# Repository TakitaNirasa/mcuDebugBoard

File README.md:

# Отладочная плата
### Назначение
Унивесальная плата для разработки простых дешёвых встраиваемых устройств либо как вспомагательная плата в более сложной системе.
Архитектура платы представлена ниже:

### Задачи поставленные перед платой:
  * Максимальная дешивизна и простота в покупке компонентов
  * "Универсальность без излишеств"
  * Возможность подключения периферии без мотка проводов
  * Наличие как обычного ввода-вывода, так и опторазвязанного
  * Наличие "силовой части" управления нагрузкой
  * Кнопки и индикация на плате
  * Модуль зарядки аккумулятора с защитой

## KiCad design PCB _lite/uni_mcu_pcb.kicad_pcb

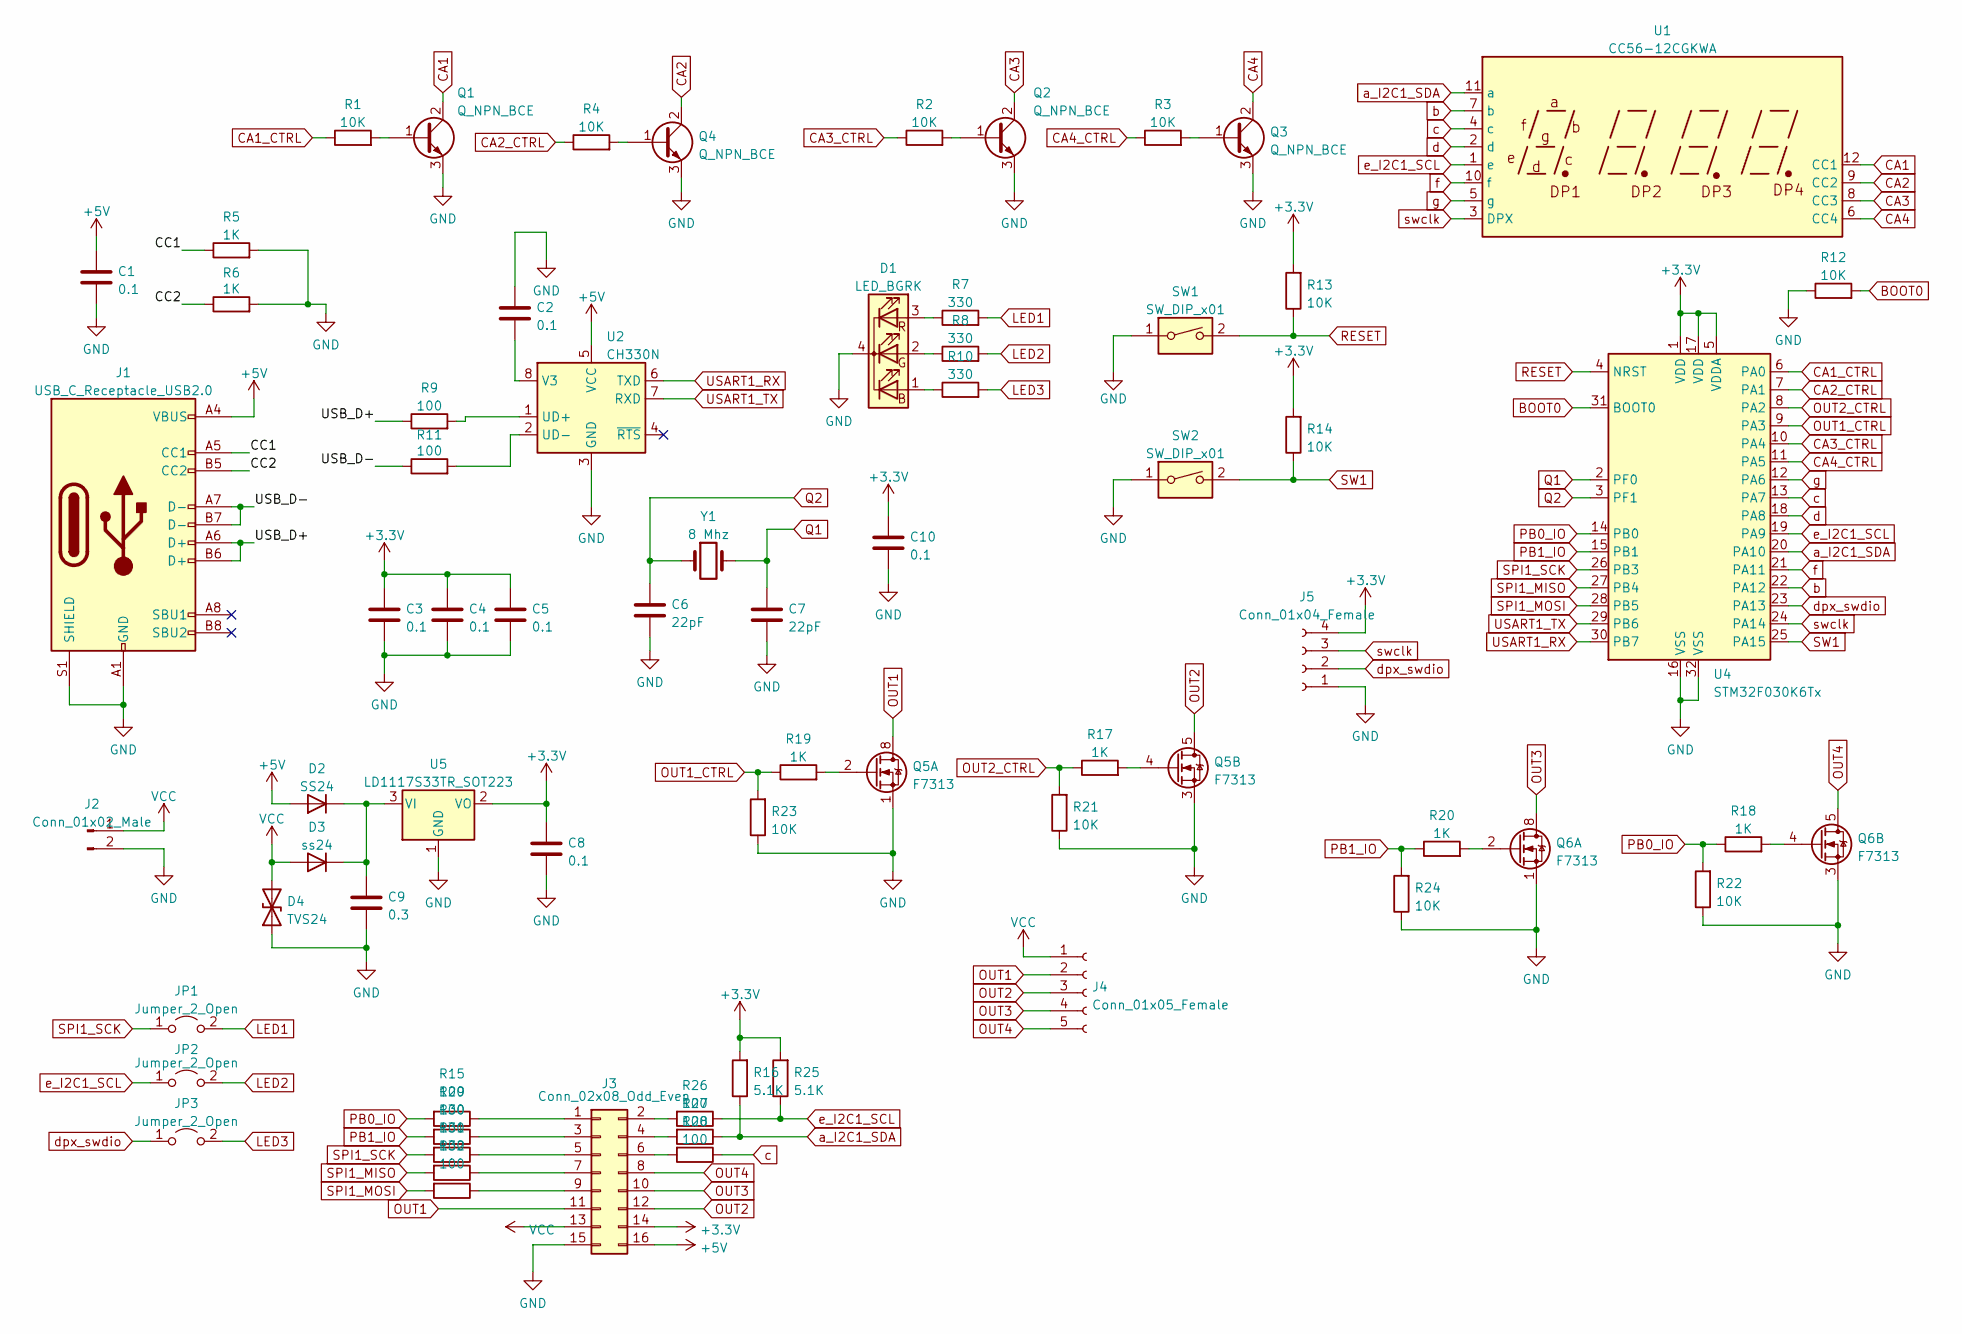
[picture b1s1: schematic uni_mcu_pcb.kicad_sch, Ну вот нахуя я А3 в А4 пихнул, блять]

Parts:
C1, C2, C3, C4, C5, C8, C10: 0.1; C_0603_1608Metric_Pad1.08x0.95mm_HandSolder
C6, C7: 22pF; C_0603_1608Metric_Pad1.08x0.95mm_HandSolder
C9: 0.3; C_0603_1608Metric_Pad1.08x0.95mm_HandSolder
D1: LED_BGRK; LED_RGB_1210
D2: SS24; D_SMB
D3: ss24; D_SMB
D4: TVS24; D_SMB
J1: USB_C_Receptacle_USB2.0; USB_C_Receptacle_GCT_USB4105-xx-A_16P_TopMnt_Horizontal
J2: Conn_01x02_Male; TerminalBlock_MetzConnect_Type011_RT05502HBWC_1x02_P5.00mm_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
J3: Conn_02x08_Odd_Even; IDC-Header_2x08_P2.54mm_Vertical
J4: Conn_01x05_Female; TerminalBlock_MetzConnect_Type011_RT05505HBWC_1x05_P5.00mm_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
J5: Conn_01x04_Female; Hirose_DF11-4DP-2DSA_2x02_P2.00mm_Vertical
JP1, JP2, JP3: Jumper_2_Open; SolderJumper-2_P1.3mm_Open_TrianglePad1.0x1.5mm
Q1, Q2, Q3, Q4: Q_NPN_BCE; SOT-23-3
Q5, Q6: F7313; SOIC-8_3.9x4.9mm_P1.27mm
R1, R2, R3, R4, R12, R13, R14, R21, R22, R23, R24: 10K; R_0603_1608Metric_Pad0.98x0.95mm_HandSolder
R5, R6, R17, R18, R19, R20: 1K; R_0603_1608Metric_Pad0.98x0.95mm_HandSolder
R7, R8, R10: 330; R_0603_1608Metric_Pad0.98x0.95mm_HandSolder
R9, R11, R15, R26, R27, R28, R29, R30, R31, R32: 100; R_0603_1608Metric_Pad0.98x0.95mm_HandSolder
R16, R25: 5.1K; R_0603_1608Metric_Pad0.98x0.95mm_HandSolder
SW1, SW2: SW_DIP_x01; SW_SPST_CK_RS282G05A3
U1: CC56-12CGKWA; CA56-12CGKWA
U2: CH330N; SOIC-8_3.9x4.9mm_P1.27mm
U4: STM32F030K6Tx; LQFP-32_7x7mm_P0.8mm
U5: LD1117S33TR_SOT223; SOT-223-3_TabPin2
Y1: 8 Mhz; Crystal_HC49-4H_Vertical

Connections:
+3V3: C3.1, C4.1, C5.1, C8.1, C10.1, J3.14, J5.4, R13.2, R14.2, R16.2, R25.2, U4.1 (VDD), U4.5 (VDDA), U4.17 (VDD), U5.2 (VO)
+5V: C1.1, D2.1 (A), J1.A4 (VBUS), J1.A9 (VBUS), J1.B4 (VBUS), J1.B9 (VBUS), J3.16, U2.5 (VCC)
/CC1: J1.A5 (CC1), R5.1
/CC2: J1.B5 (CC2), R6.1
/USB_D+: J1.A6 (D+), J1.B6 (D+), R9.1
/USB_D-: J1.A7 (D-), J1.B7 (D-), R11.1
BOOT0: R12.2, U4.31 (BOOT0)
CA1: Q1.2 (C), U1.12 (CC1)
CA1_CTRL: R1.1, U4.6 (PA0)
CA2: Q4.2 (C), U1.9 (CC2)
CA2_CTRL: R4.1, U4.7 (PA1)
CA3: Q2.2 (C), U1.8 (CC3)
CA3_CTRL: R2.1, U4.10 (PA4)
CA4: Q3.2 (C), U1.6 (CC4)
CA4_CTRL: R3.1, U4.11 (PA5)
GND: C1.2, C2.1, C3.2, C4.2, C5.2, C6.1, C7.2, C8.2, C9.2, C10.2, D1.4 (K), D4.1 (A1), J1.A1 (GND), J1.A12 (GND), J1.B1 (GND), J1.B12 (GND), J1.S1 (SHIELD), J2.2, J3.15, J5.1, Q1.3 (E), Q2.3 (E), Q3.3 (E), Q4.3 (E), Q5.1 (S1), Q5.3 (S2), Q6.1 (S1), Q6.3 (S2), R5.2, R6.2, R12.1, R21.1, R22.1, R23.1, R24.1, SW1.1, SW2.1, U2.3 (GND), U4.16 (VSS), U4.32 (VSS), U5.1 (GND)
LED1: JP1.2 (B), R7.2
LED2: JP2.2 (B), R8.2
LED3: JP3.2 (B), R10.2
unnamed: C2.2, U2.8 (V3)
unnamed: C9.1, D2.2 (K), D3.2 (K), U5.3 (VI)
unnamed: D1.1 (BA), R10.1
unnamed: D1.2 (GA), R8.1
unnamed: D1.3 (RA), R7.1
unnamed: J3.1, R15.1
unnamed: J3.2, R26.2
unnamed: J3.3, R29.1
unnamed: J3.4, R27.2
unnamed: J3.5, R30.1
unnamed: J3.6, R28.2
unnamed: J3.7, R31.1
unnamed: J3.9, R32.1
unnamed: Q1.1 (B), R1.2
unnamed: Q2.1 (B), R2.2
unnamed: Q3.1 (B), R3.2
unnamed: Q4.1 (B), R4.2
unnamed: Q5.2 (G1), R19.2
unnamed: Q5.4 (G2), R17.2
unnamed: Q6.2 (G1), R20.2
unnamed: Q6.4 (G2), R18.2
unnamed: R9.2, U2.1 (UD+)
unnamed: R11.2, U2.2 (UD-)
OUT1: J3.11, J4.2, Q5.7 (D1), Q5.8 (D1)
OUT1_CTRL: R19.1, R23.2, U4.9 (PA3)
OUT2: J3.12, J4.3, Q5.5 (D2), Q5.6 (D2)
OUT2_CTRL: R17.1, R21.2, U4.8 (PA2)
OUT3: J3.10, J4.4, Q6.7 (D1), Q6.8 (D1)
OUT4: J3.8, J4.5, Q6.5 (D2), Q6.6 (D2)
PB0_IO: R15.2, R18.1, R22.2, U4.14 (PB0)
PB1_IO: R20.1, R24.2, R29.2, U4.15 (PB1)
Q1: C7.1, U4.2 (PF0), Y1.2
Q2: C6.2, U4.3 (PF1), Y1.1
RESET: R13.1, SW1.2, U4.4 (NRST)
SPI1_MISO: R31.2, U4.27 (PB4)
SPI1_MOSI: R32.2, U4.28 (PB5)
SPI1_SCK: JP1.1 (A), R30.2, U4.26 (PB3)
SW1: R14.1, SW2.2, U4.25 (PA15)
USART1_RX: U2.6 (TXD), U4.30 (PB7)
USART1_TX: U2.7 (RXD), U4.29 (PB6)
VCC: D3.1 (A), D4.2 (A2), J2.1, J3.13, J4.1
a_I2C1_SDA: R16.1, R27.1, U1.11 (a), U4.20 (PA10)
b: U1.7 (b), U4.22 (PA12)
c: R28.1, U1.4 (c), U4.13 (PA7)
d: U1.2 (d), U4.18 (PA8)
dpx_swdio: J5.2, JP3.1 (A), U4.23 (PA13)
e_I2C1_SCL: JP2.1 (A), R25.1, R26.1, U1.1 (e), U4.19 (PA9)
f: U1.10 (f), U4.21 (PA11)
g: U1.5 (g), U4.12 (PA6)
swclk: J5.3, U1.3 (DPX), U4.24 (PA14)

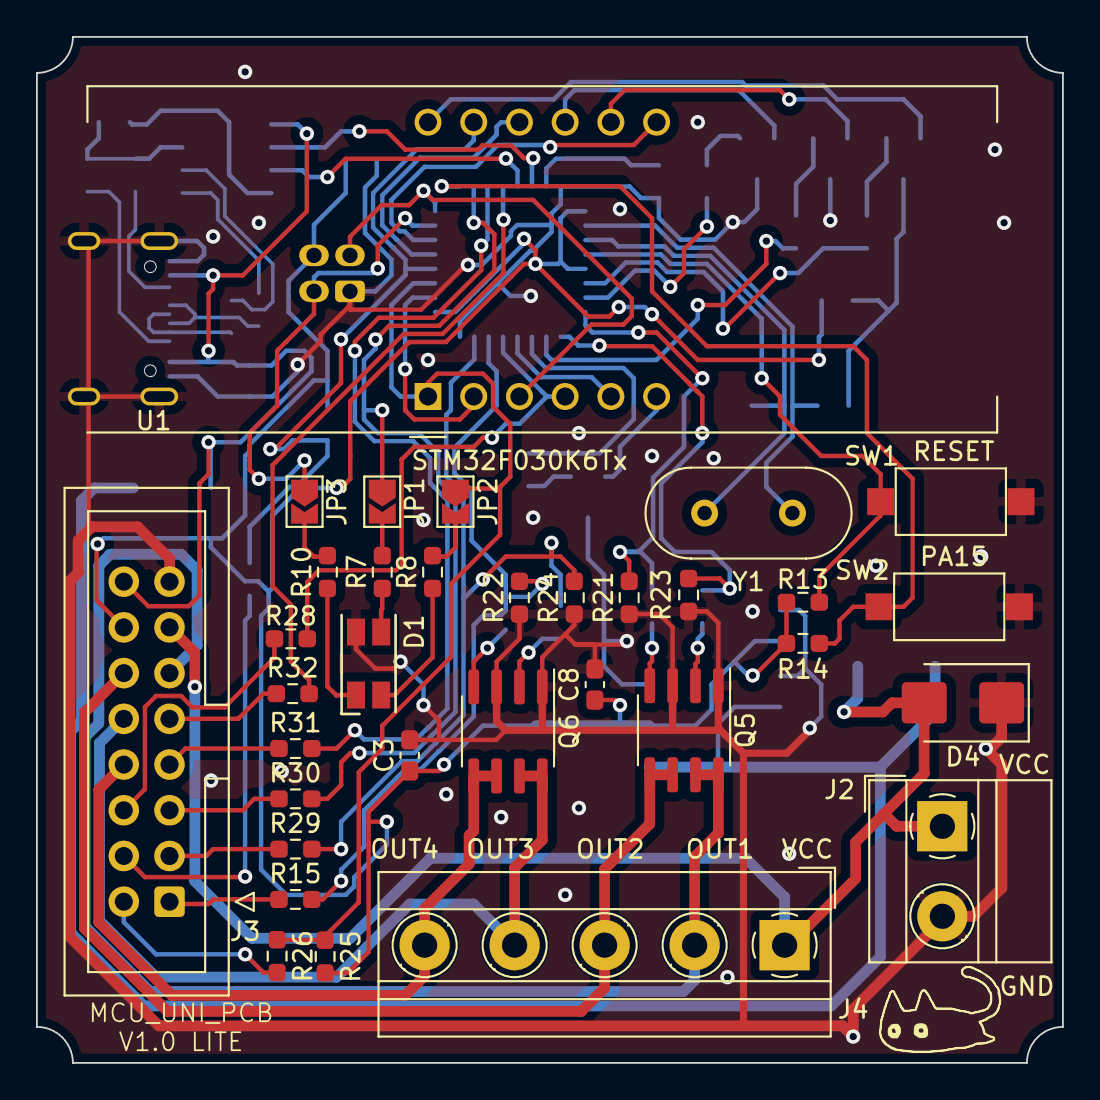
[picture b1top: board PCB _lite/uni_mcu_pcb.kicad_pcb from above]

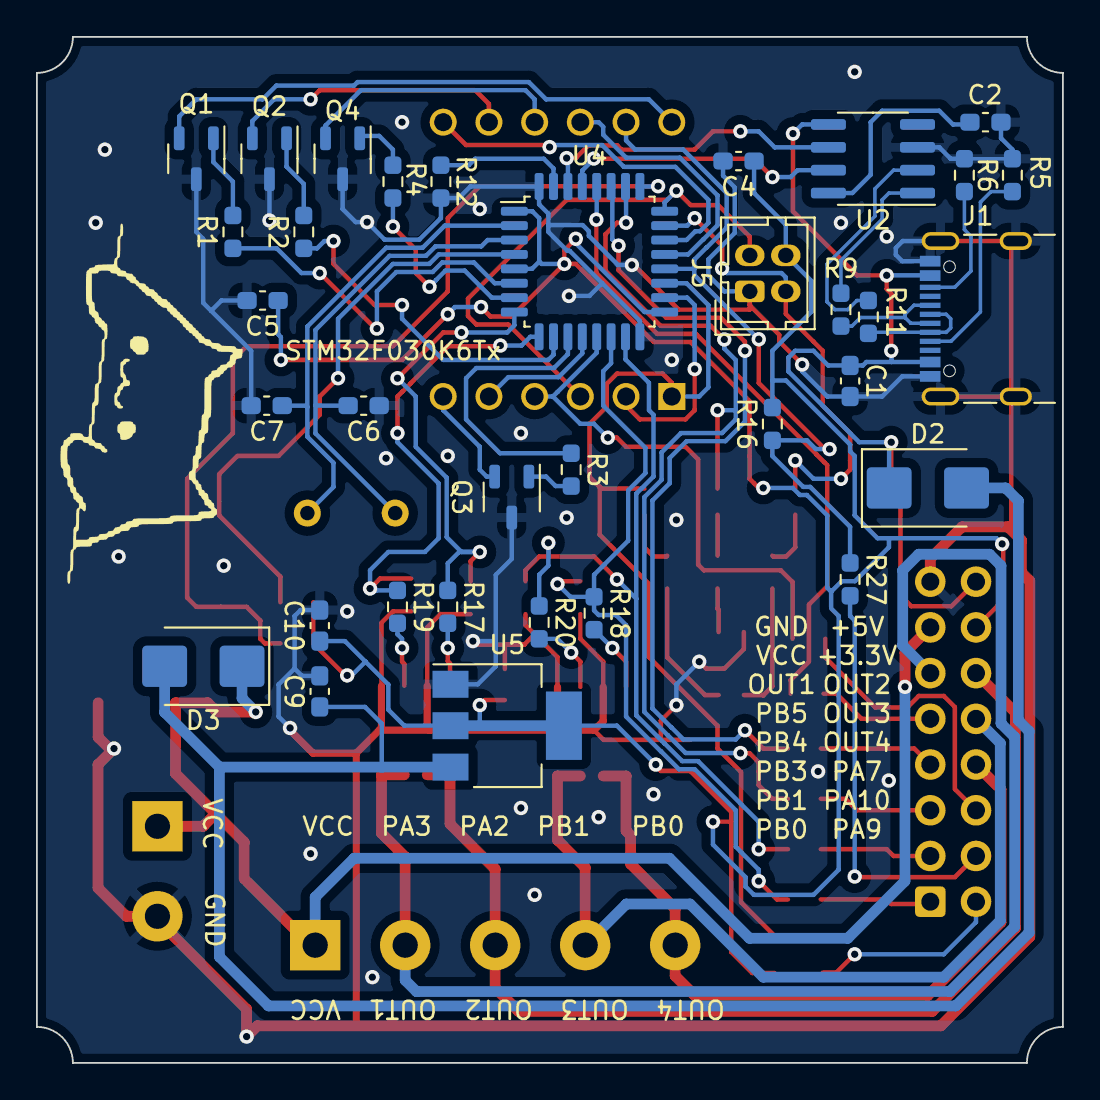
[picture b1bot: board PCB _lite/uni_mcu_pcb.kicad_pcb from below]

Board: 2 copper layers, 57.0 x 57.0 mm, 67 parts (34 on the bottom side), 69 nets.

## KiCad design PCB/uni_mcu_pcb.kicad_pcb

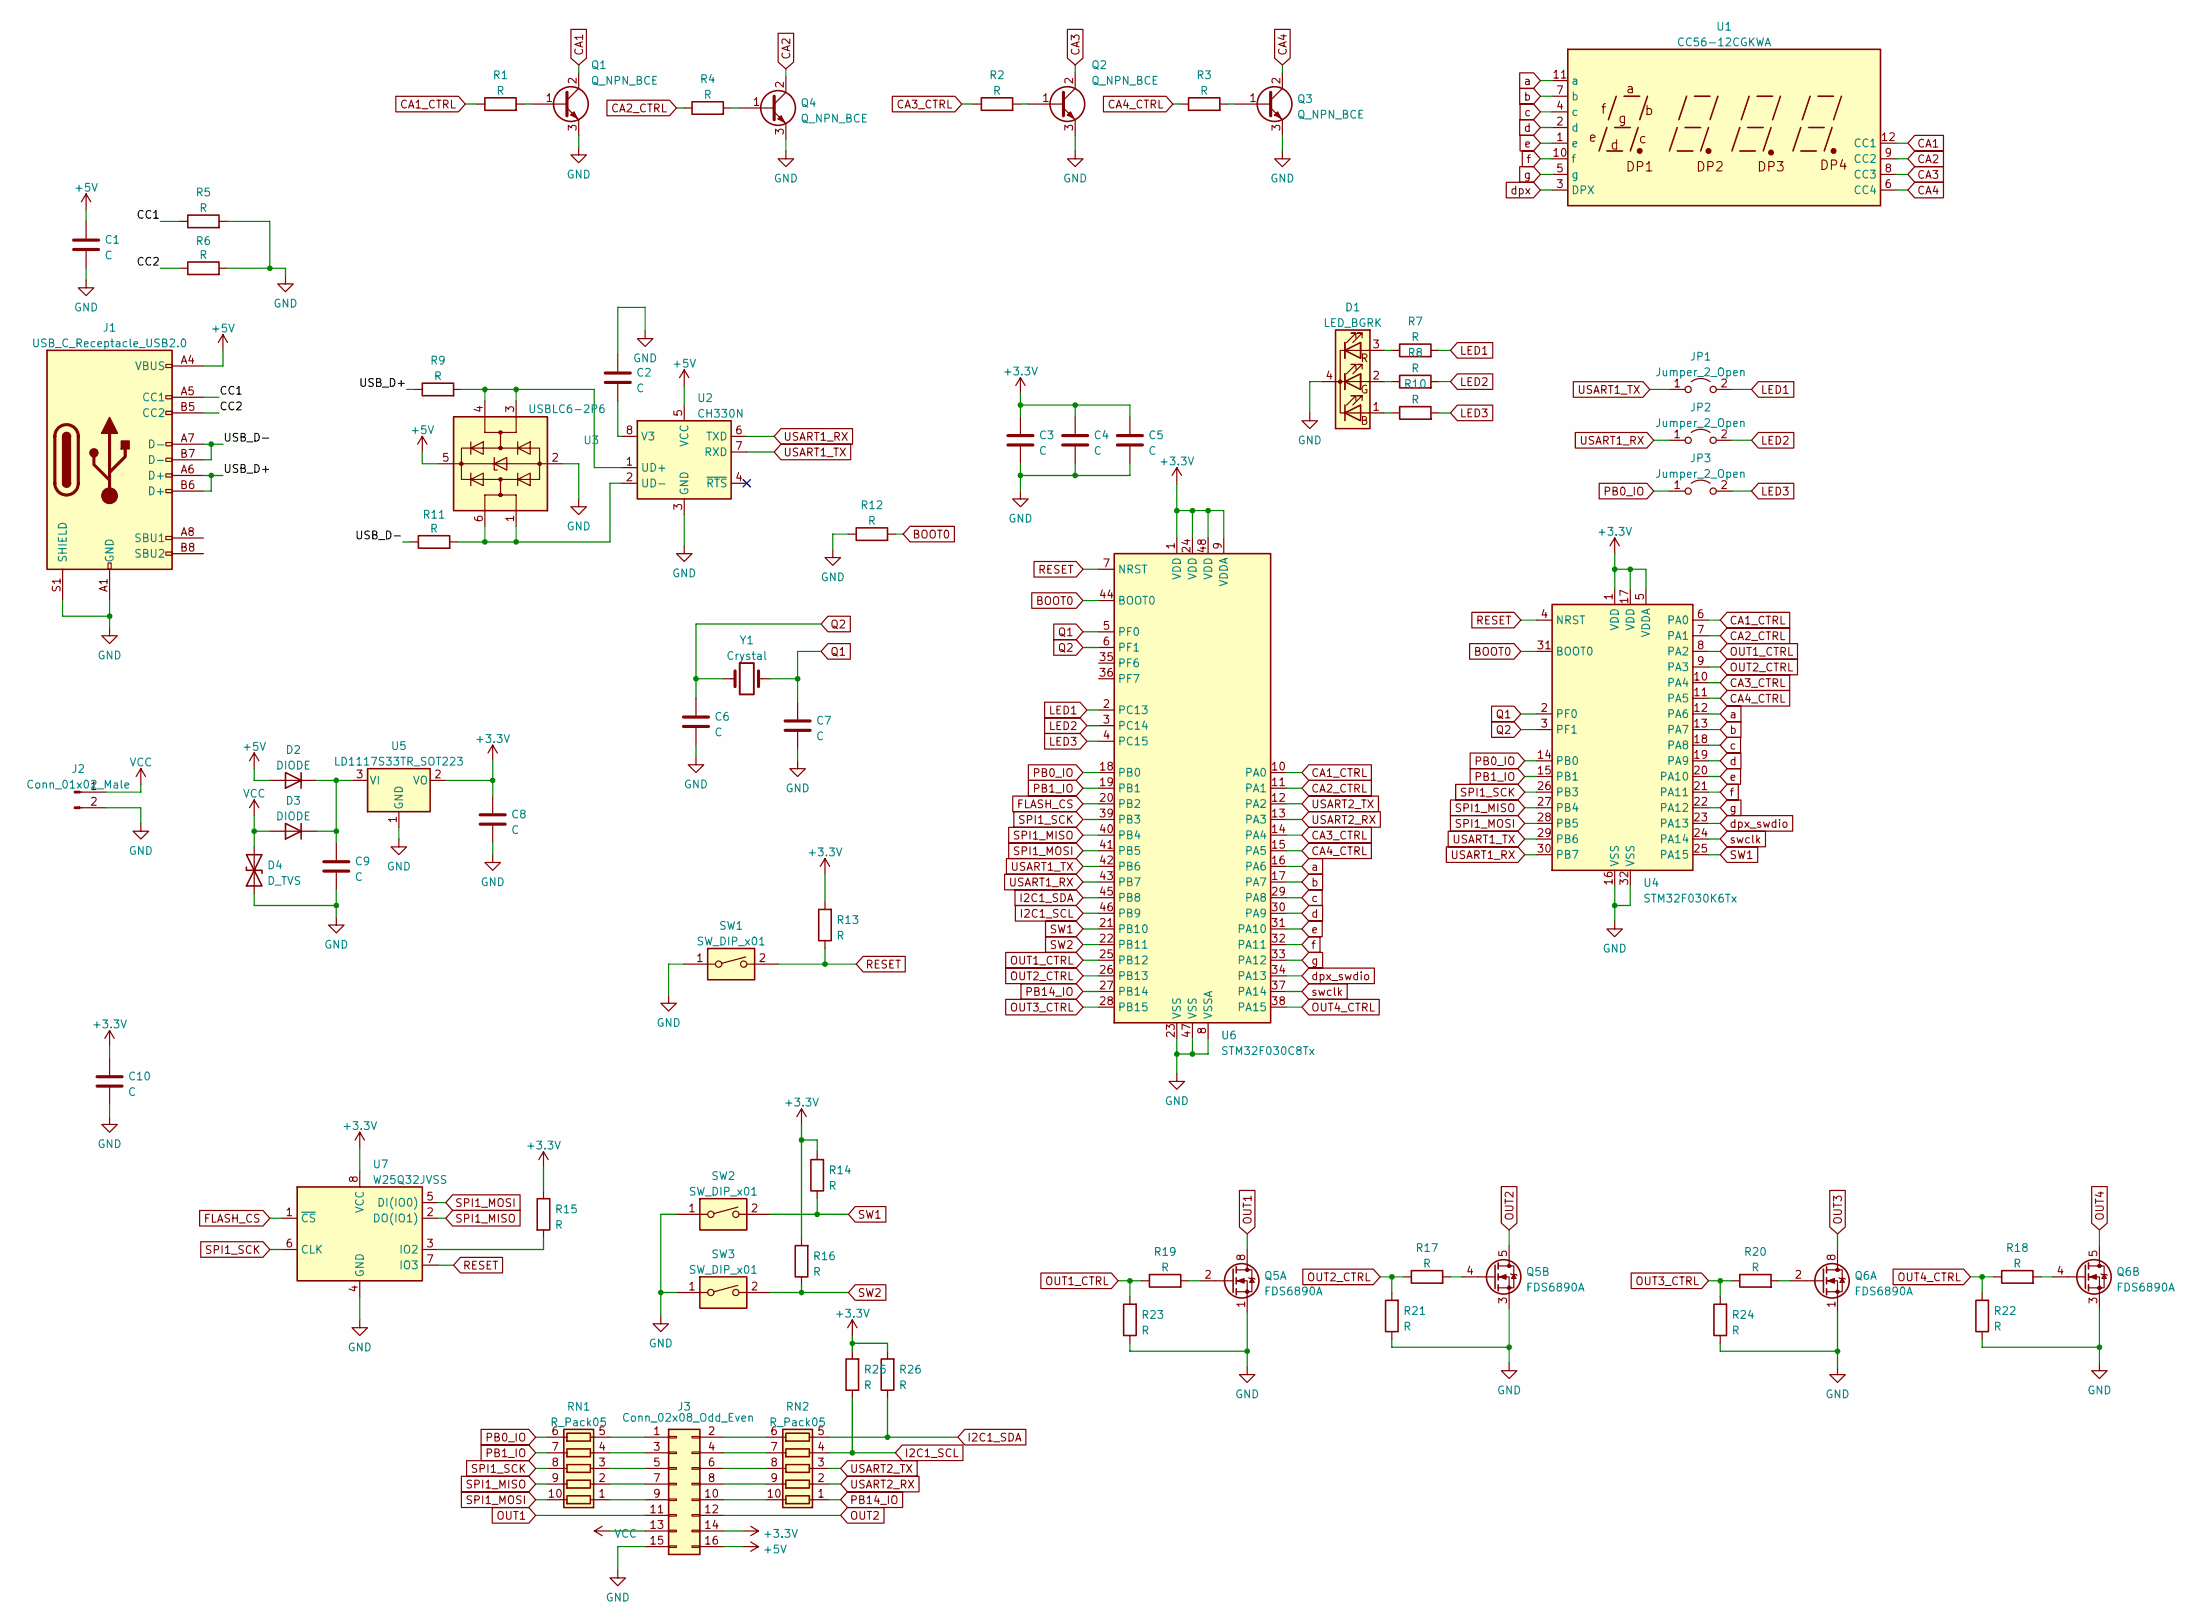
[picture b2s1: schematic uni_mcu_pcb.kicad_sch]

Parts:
C1, C2, C3, C4, C5, C6, C7, C8, C9, C10: C; C_0603_1608Metric_Pad1.08x0.95mm_HandSolder
D1: LED_BGRK; LED_RGB_1210
D2, D3: DIODE; D_SMB
D4: D_TVS; D_SMB
J1: USB_C_Receptacle_USB2.0; USB_C_Receptacle_GCT_USB4105-xx-A_16P_TopMnt_Horizontal
J2: Conn_01x02_Male; PinHeader_1x02_P2.54mm_Vertical
J3: Conn_02x08_Odd_Even; IDC-Header_2x08_P2.54mm_Vertical
JP1, JP2, JP3: Jumper_2_Open; SolderJumper-2_P1.3mm_Open_TrianglePad1.0x1.5mm
Q1, Q2, Q3, Q4: Q_NPN_BCE; SOT-23-3
Q5, Q6: FDS6890A; SOIC-8_3.9x4.9mm_P1.27mm
R1, R2, R3, R4, R5, R6, R7, R8, R9, R10, R11, R12, R13, R14, R15, R16, R17, R18, R19, R20, R21, R22, R23, R24, R25, R26: R; R_0603_1608Metric_Pad0.98x0.95mm_HandSolder
RN1, RN2: R_Pack05; R_Array_Convex_5x0603
SW1, SW2, SW3: SW_DIP_x01; SW_Push_1P1T_NO_Vertical_Wuerth_434133025816
U1: CC56-12CGKWA; CA56-12CGKWA
U2: CH330N; SOIC-8_3.9x4.9mm_P1.27mm
U3: USBLC6-2P6; SOT-666
U4: STM32F030K6Tx; LQFP-32_7x7mm_P0.8mm
U5: LD1117S33TR_SOT223; SOT-223-3_TabPin2
U6: STM32F030C8Tx; LQFP-48_7x7mm_P0.5mm
U7: W25Q32JVSS; SOIC-8_5.23x5.23mm_P1.27mm
Y1: Crystal; Crystal_HC49-4H_Vertical

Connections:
+3V3: C3.1, C4.1, C5.1, C8.1, C10.1, J3.14, R13.2, R14.2, R15.1, R16.2, R25.2, R26.2, U4.1 (VDD), U4.5 (VDDA), U4.17 (VDD), U5.2 (VO), U6.1 (VDD), U6.9 (VDDA), U6.24 (VDD), U6.48 (VDD), U7.8 (VCC)
+5V: C1.1, D2.1 (A), J1.A4 (VBUS), J1.A9 (VBUS), J1.B4 (VBUS), J1.B9 (VBUS), J3.16, U2.5 (VCC), U3.5 (VBUS)
/CC1: J1.A5 (CC1), R5.1
/CC2: J1.B5 (CC2), R6.1
/USB_D+: J1.A6 (D+), J1.B6 (D+), R9.1
/USB_D-: J1.A7 (D-), J1.B7 (D-), R11.1
BOOT0: R12.2, U4.31 (BOOT0), U6.44 (BOOT0)
CA1: Q1.2 (C), U1.12 (CC1)
CA1_CTRL: R1.1, U4.6 (PA0), U6.10 (PA0)
CA2: Q4.2 (C), U1.9 (CC2)
CA2_CTRL: R4.1, U4.7 (PA1), U6.11 (PA1)
CA3: Q2.2 (C), U1.8 (CC3)
CA3_CTRL: R2.1, U4.10 (PA4), U6.14 (PA4)
CA4: Q3.2 (C), U1.6 (CC4)
CA4_CTRL: R3.1, U4.11 (PA5), U6.15 (PA5)
FLASH_CS: U6.20 (PB2), U7.1 (~CS)
GND: C1.2, C2.1, C3.2, C4.2, C5.2, C6.1, C7.2, C8.2, C9.2, C10.2, D1.4 (K), D4.1 (A1), J1.A1 (GND), J1.A12 (GND), J1.B1 (GND), J1.B12 (GND), J1.S1 (SHIELD), J2.2, J3.15, Q1.3 (E), Q2.3 (E), Q3.3 (E), Q4.3 (E), Q5.1 (S1), Q5.3 (S2), Q6.1 (S1), Q6.3 (S2), R5.2, R6.2, R12.1, R21.1, R22.1, R23.1, R24.1, SW1.1, SW2.1, SW3.1, U2.3 (GND), U3.2 (GND), U4.16 (VSS), U4.32 (VSS), U5.1 (GND), U6.8 (VSSA), U6.23 (VSS), U6.47 (VSS), U7.4 (GND)
I2C1_SCL: R25.1, RN2.4 (R4.1), U6.46 (PB9)
I2C1_SDA: R26.1, RN2.5 (R5.1), U6.45 (PB8)
LED1: JP1.2 (B), R7.2, U6.2 (PC13)
LED2: JP2.2 (B), R8.2, U6.3 (PC14)
LED3: JP3.2 (B), R10.2, U6.4 (PC15)
unnamed: C2.2, U2.8 (V3)
unnamed: C9.1, D2.2 (K), D3.2 (K), U5.3 (VI)
unnamed: D1.1 (BA), R10.1
unnamed: D1.2 (GA), R8.1
unnamed: D1.3 (RA), R7.1
unnamed: J3.1, RN1.5 (R5.1)
unnamed: J3.2, RN2.6 (R5.2)
unnamed: J3.3, RN1.4 (R4.1)
unnamed: J3.4, RN2.7 (R4.2)
unnamed: J3.5, RN1.3 (R3.1)
unnamed: J3.6, RN2.8 (R3.2)
unnamed: J3.7, RN1.2 (R2.1)
unnamed: J3.8, RN2.9 (R2.2)
unnamed: J3.9, RN1.1 (R1.1)
unnamed: J3.10, RN2.10 (R1.2)
unnamed: Q1.1 (B), R1.2
unnamed: Q2.1 (B), R2.2
unnamed: Q3.1 (B), R3.2
unnamed: Q4.1 (B), R4.2
unnamed: Q5.2 (G1), R19.2
unnamed: Q5.4 (G2), R17.2
unnamed: Q6.2 (G1), R20.2
unnamed: Q6.4 (G2), R18.2
unnamed: R9.2, U2.1 (UD+), U3.3 (I/O2), U3.4 (I/O2)
unnamed: R11.2, U2.2 (UD-), U3.1 (I/O1), U3.6 (I/O1)
unnamed: R15.2, U7.3 (IO2)
OUT1: J3.11, Q5.7 (D1), Q5.8 (D1)
OUT1_CTRL: R19.1, R23.2, U4.8 (PA2), U6.25 (PB12)
OUT2: J3.12, Q5.5 (D2), Q5.6 (D2)
OUT2_CTRL: R17.1, R21.2, U4.9 (PA3), U6.26 (PB13)
OUT3: Q6.7 (D1), Q6.8 (D1)
OUT3_CTRL: R20.1, R24.2, U6.28 (PB15)
OUT4: Q6.5 (D2), Q6.6 (D2)
OUT4_CTRL: R18.1, R22.2, U6.38 (PA15)
PB0_IO: JP3.1 (A), RN1.6 (R5.2), U4.14 (PB0), U6.18 (PB0)
PB1_IO: RN1.7 (R4.2), U4.15 (PB1), U6.19 (PB1)
PB14_IO: RN2.1 (R1.1), U6.27 (PB14)
Q1: C7.1, U4.2 (PF0), U6.5 (PF0), Y1.2
Q2: C6.2, U4.3 (PF1), U6.6 (PF1), Y1.1
RESET: R13.1, SW1.2, U4.4 (NRST), U6.7 (NRST), U7.7 (IO3)
SPI1_MISO: RN1.9 (R2.2), U4.27 (PB4), U6.40 (PB4), U7.2 (DO(IO1))
SPI1_MOSI: RN1.10 (R1.2), U4.28 (PB5), U6.41 (PB5), U7.5 (DI(IO0))
SPI1_SCK: RN1.8 (R3.2), U4.26 (PB3), U6.39 (PB3), U7.6 (CLK)
SW1: R14.1, SW2.2, U4.25 (PA15), U6.21 (PB10)
SW2: R16.1, SW3.2, U6.22 (PB11)
USART1_RX: JP2.1 (A), U2.6 (TXD), U4.30 (PB7), U6.43 (PB7)
USART1_TX: JP1.1 (A), U2.7 (RXD), U4.29 (PB6), U6.42 (PB6)
USART2_RX: RN2.2 (R2.1), U6.13 (PA3)
USART2_TX: RN2.3 (R3.1), U6.12 (PA2)
VCC: D3.1 (A), D4.2 (A2), J2.1, J3.13
a: U1.11 (a), U4.12 (PA6), U6.16 (PA6)
b: U1.7 (b), U4.13 (PA7), U6.17 (PA7)
c: U1.4 (c), U4.18 (PA8), U6.29 (PA8)
d: U1.2 (d), U4.19 (PA9), U6.30 (PA9)
dpx: U1.3 (DPX)
dpx_swdio: U4.23 (PA13), U6.34 (PA13)
e: U1.1 (e), U4.20 (PA10), U6.31 (PA10)
f: U1.10 (f), U4.21 (PA11), U6.32 (PA11)
g: U1.5 (g), U4.22 (PA12), U6.33 (PA12)
swclk: U4.24 (PA14), U6.37 (PA14)

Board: 2 copper layers, 65 parts (0 on the bottom side), 81 nets, no tracks yet.

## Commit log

2023-03-17 Первый коммит
2023-03-17 Пикча
2023-03-17 Добавлены некоторые компоненты на плату
2023-03-21 Схемотехника разработана на 80%
2023-03-21 Добавлено управление нагрузкой
2023-03-23 Добавлен кварц. Нужно добавить модуль заряда
2023-03-23 Добавлен ещё один контроллер, но в QFP32 корпусе
2023-03-24 Начата разводка платы
2023-03-27 Добавлены библиотеки для зарядки li-ion
2023-03-31 Разводка модуля зарядки li-ion
2023-05-24 Добавлена lite версия платы
2023-05-24 Частично разведена плата
2023-05-25 разведена плата
2023-05-26 Расставлены номиналы
2023-05-26 Отредактирована распиновка, доделана шелкография
2023-05-26 Схема теперь А4, Сформированы герберы
2023-05-26 Утолщение кота
2023-05-27 Правка 3д и добавлен скрин модели
